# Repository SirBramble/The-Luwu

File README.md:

# The Luwu

ESP32 Board for RGB LED integration into Home Assistant

## Motivation

My 3D Printer has a standard RGB LED Strip installed in its enclosure. This Board allows me to control it with Home Assistant. There are easier and cheaper ways of doing this, but this Board also doubled as a test board for implementing Ideal Diodes and MOSFET drivers.

## Features

The Board uses a ESP32C3 to interface with Home Assistant. The ESP controls 3 RGB channels that are each capable of (in theory) driving 10A. These channels can also be mapped to control addressable RGB Strips, although this can only be done for all channels at once and **ONLY** if the level shifter logic voltage is set to 5V. There is also one dedicated addressable RGB Strip Port, that can be used at any time.

To accomplish these features, it needs a 5V supply to drive the logic and optionally the addressable LED Strips and a 12V supply to drive the non addressable Strip. To accomplish this in a 3D Printer environment a Voltage converter for the 24V Power Supply is needed. For this [the Supluwu](https://github.com/SirBramble/The-Supluwu) could be used.

## Integration into Home Assistant

ESP Home Config:

```yaml
esphome:
  name: NAME
  friendly_name: FRIENDLY_NAME

esp32:
  board: esp32-c3-devkitm-1
  framework:
    type: arduino

# Enable logging
logger:
  level: DEBUG
# Enable Home Assistant API
api:
  encryption:
    key: ""     #let this auto generate or set it yourself

ota:
  password: ""  #let this auto generate or set it yourself

wifi:
  ssid: !secret wifi_ssid
  password: !secret wifi_password

  # Enable fallback hotspot (captive portal) in case wifi connection fails
  ap:
    ssid: "FALLBACK_HOTSPOT_NAME"
    password: "SUPER_SECURE_PASSWORD123"

light:
  - platform: rgb
    id: oldstyle_rgb
    name: "Oldstyle RGB"
    red: gpio_red
    green: gpio_green
    blue: gpio_blue
    effects:
      - lambda:
          name: Rainbow
          update_interval: 5s
          lambda: |-
            static int state = 0;
            auto call = id(oldstyle_rgb).turn_on();
            call.set_transition_length(4000);
            if (state == 0) {
              call.set_rgb(1.0, 0.0, 0.0);
            } else if (state == 1) {
              call.set_rgb(1.0, 0.5, 0.0);
            } else if (state == 2) {
              call.set_rgb(1.0, 1.0, 0.0);
            } else if (state == 3) {
              call.set_rgb(0.5, 1.0, 0.0);
            } else if (state == 4) {
              call.set_rgb(0.0, 1.0, 0.0);
            } else if (state == 5) {
              call.set_rgb(0.0, 1.0, 0.5);
            } else if (state == 6) {
              call.set_rgb(0.0, 1.0, 1.0);
            } else if (state == 7) {
              call.set_rgb(0.0, 0.5, 1.0);
            } else if (state == 8) {
              call.set_rgb(0.0, 0.0, 1.0);
            } else if (state == 9) {
              call.set_rgb(0.5, 0.0, 1.0);
            } else if (state == 10) {
              call.set_rgb(1.0, 0.0, 1.0);
            } else if (state == 11) {
              call.set_rgb(1.0, 0.0, 0.5);
            }
            call.perform();
            state++;
            if (state == 12)
              state = 0;
      - lambda:
            name: Fast Rainbow
            update_interval: 1s
            lambda: |-
              static int state = 0;
              auto call = id(oldstyle_rgb).turn_on();
              call.set_transition_length(1000);
              if (state == 0) {
                call.set_rgb(1.0, 0.0, 0.0);
              } else if (state == 1) {
                call.set_rgb(1.0, 0.5, 0.0);
              } else if (state == 2) {
                call.set_rgb(1.0, 1.0, 0.0);
              } else if (state == 3) {
                call.set_rgb(0.5, 1.0, 0.0);
              } else if (state == 4) {
                call.set_rgb(0.0, 1.0, 0.0);
              } else if (state == 5) {
                call.set_rgb(0.0, 1.0, 0.5);
              } else if (state == 6) {
                call.set_rgb(0.0, 1.0, 1.0);
              } else if (state == 7) {
                call.set_rgb(0.0, 0.5, 1.0);
              } else if (state == 8) {
                call.set_rgb(0.0, 0.0, 1.0);
              } else if (state == 9) {
                call.set_rgb(0.5, 0.0, 1.0);
              } else if (state == 10) {
                call.set_rgb(1.0, 0.0, 1.0);
              } else if (state == 11) {
                call.set_rgb(1.0, 0.0, 0.5);
              }
              call.perform();
              state++;
              if (state == 12)
                state = 0;

# Example output entry (default)
output:
  - platform: ledc
    id: gpio_red
    pin: GPIO6
  - platform: ledc
    id: gpio_green
    pin: GPIO7
  - platform: ledc
    id: gpio_blue
    pin: GPIO10

#uncomment to enable
# Example output entry (modified)
#output:
#  - platform: ledc
#    id: gpio_red
#    pin: GPIO7
#  - platform: ledc
#    id: gpio_green
#    pin: GPIO10
#  - platform: ledc
#    id: gpio_blue
#    pin: GPIO6

captive_portal:
    
```

### Flashing firmware

I had some issues when flashing the Firmware.

This helped: [https://github.com/espressif/esp-idf/issues/9005](https://github.com/espressif/esp-idf/issues/9005)

## Schematic

The Schematic can be found here: [The Luwu PCB/print/The Luwu PCB.pdf](https://github.com/SirBramble/The-Luwu/blob/f4439437ab35bf7dc6665ce1337c5cff792b409b/The%20Luwu%20PCB/print/The%20Luwu%20PCB.pdf)

## Pictures

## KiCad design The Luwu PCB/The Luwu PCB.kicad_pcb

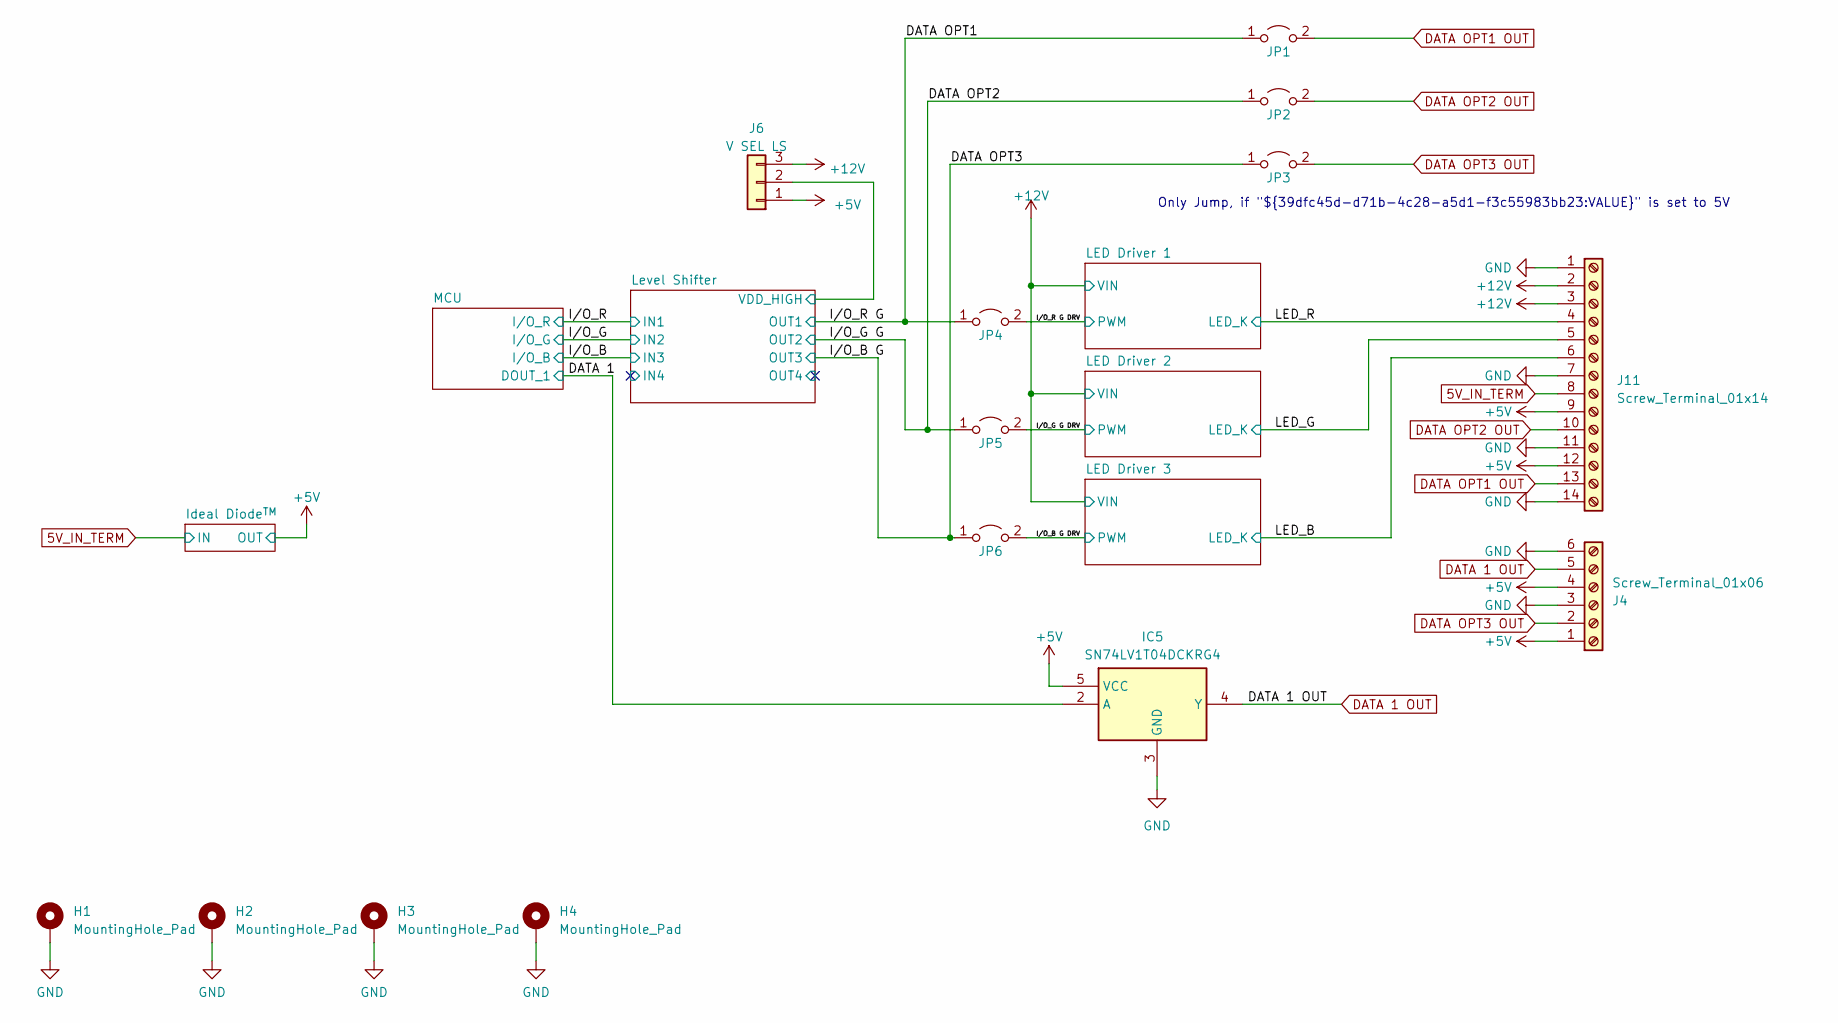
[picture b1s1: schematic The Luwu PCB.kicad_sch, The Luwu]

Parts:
H1, H2, H3, H4: MountingHole_Pad; MountingHole_3.2mm_M3_DIN965_Pad
IC5: SN74LV1T04DCKRG4; SOT65P210X110-5N; Mouser Part Number 595-SN74LV1T04DCKRG4
J4: Screw_Terminal_01x06; TerminalBlock_bornier-6_P5.08mm
J6: V SEL LS; PinHeader_1x03_P2.54mm_Vertical
J11: Screw_Terminal_01x14; TerminalBlock_bornier-14_P5.08mm
JP1, JP2, JP3, JP4, JP5, JP6: Jumper_2_Open; PinHeader_1x02_P2.54mm_Vertical

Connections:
5V_IN_TERM: J11.8; also elsewhere on the board
+5V: IC5.5 (VCC), J4.1, J4.4, J6.1, J11.9, J11.12; also elsewhere on the board
+12V: J6.3, J11.2, J11.3; also elsewhere on the board
/DATA 1: IC5.2 (A); also elsewhere on the board
/DATA OPT1: JP1.1 (A), JP4.1 (A); also elsewhere on the board
/DATA OPT2: JP2.1 (A), JP5.1 (A); also elsewhere on the board
/DATA OPT3: JP3.1 (A), JP6.1 (A); also elsewhere on the board
/I/O_B G DRV: JP6.2 (B); also elsewhere on the board
/I/O_G G DRV: JP5.2 (B); also elsewhere on the board
/I/O_R G DRV: JP4.2 (B); also elsewhere on the board
/LED_B: J11.6; also elsewhere on the board
/LED_G: J11.5; also elsewhere on the board
/LED_R: J11.4; also elsewhere on the board
/Level Shifter/VDD_HIGH: J6.2; also elsewhere on the board
DATA 1 OUT: IC5.4 (Y), J4.5
DATA OPT1 OUT: J11.13, JP1.2 (B)
DATA OPT2 OUT: J11.10, JP2.2 (B)
DATA OPT3 OUT: J4.2, JP3.2 (B)
GND: H1.1, H2.1, H3.1, H4.1, IC5.3 (GND), J4.3, J4.6, J11.1, J11.7, J11.11, J11.14; also elsewhere on the board

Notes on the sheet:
Only Jump, if "${39dfc45d-d71b-4c28-a5d1-f3c55983bb23:VALUE}" is set to 5V

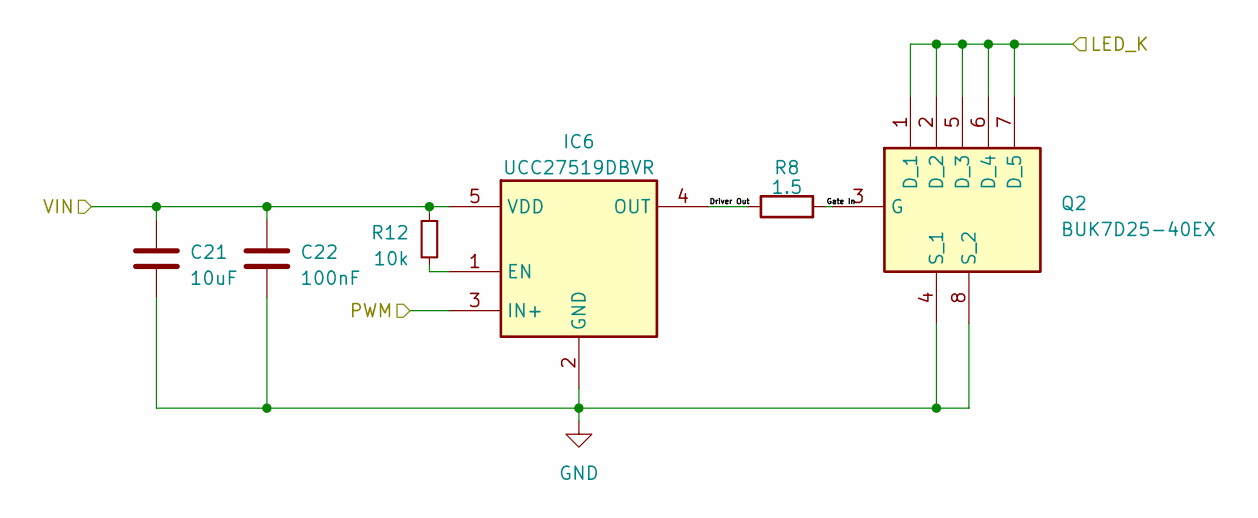
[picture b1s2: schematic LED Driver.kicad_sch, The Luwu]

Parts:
C21: 10uF; C_0603_1608Metric
C22: 100nF; C_0603_1608Metric
IC6: UCC27519DBVR; SOT95P280X145-5N; Mouser Part Number 595-UCC27519DBVR
Q2: BUK7D25-40EX; BUK7D2540EX; Mouser Part Number 771-BUK7D25-40EX
R8: 1.5; R_1206_3216Metric
R12: 10k; R_0603_1608Metric

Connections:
+12V: C21.1, C22.1, IC6.5 (VDD), R12.1; also elsewhere on the board
/I/O_R G DRV: IC6.3 (IN+); also elsewhere on the board
/LED Driver 1/Driver Out: IC6.4 (OUT), R8.1
/LED Driver 1/Gate In: Q2.3 (G), R8.2
/LED_R: Q2.1 (D_1), Q2.2 (D_2), Q2.5 (D_3), Q2.6 (D_4), Q2.7 (D_5); also elsewhere on the board
GND: C21.2, C22.2, IC6.2 (GND), Q2.4 (S_1), Q2.8 (S_2); also elsewhere on the board
unnamed: IC6.1 (EN), R12.2

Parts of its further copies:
C23, C25: 10uF; C_0603_1608Metric
C24, C26: 100nF; C_0603_1608Metric
IC7, IC8: UCC27519DBVR; SOT95P280X145-5N; Mouser Part Number 595-UCC27519DBVR
Q3, Q4: BUK7D25-40EX; BUK7D2540EX; Mouser Part Number 771-BUK7D25-40EX
R13, R15: 1.5; R_1206_3216Metric
R14, R16: 10k; R_0603_1608Metric

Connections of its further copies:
+12V: C23.1, C24.1, C25.1, C26.1, IC7.5 (VDD), IC8.5 (VDD), R14.1, R16.1; also elsewhere on the board
/I/O_B G DRV: IC8.3 (IN+); also elsewhere on the board
/I/O_G G DRV: IC7.3 (IN+); also elsewhere on the board
/LED Driver 2/Driver Out: IC7.4 (OUT), R13.1
/LED Driver 2/Gate In: Q3.3 (G), R13.2
/LED Driver 3/Driver Out: IC8.4 (OUT), R15.1
/LED Driver 3/Gate In: Q4.3 (G), R15.2
/LED_B: Q4.1 (D_1), Q4.2 (D_2), Q4.5 (D_3), Q4.6 (D_4), Q4.7 (D_5); also elsewhere on the board
/LED_G: Q3.1 (D_1), Q3.2 (D_2), Q3.5 (D_3), Q3.6 (D_4), Q3.7 (D_5); also elsewhere on the board
GND: C23.2, C24.2, C25.2, C26.2, IC7.2 (GND), IC8.2 (GND), Q3.4 (S_1), Q3.8 (S_2), Q4.4 (S_1), Q4.8 (S_2); also elsewhere on the board
unnamed: IC7.1 (EN), R14.2
unnamed: IC8.1 (EN), R16.2

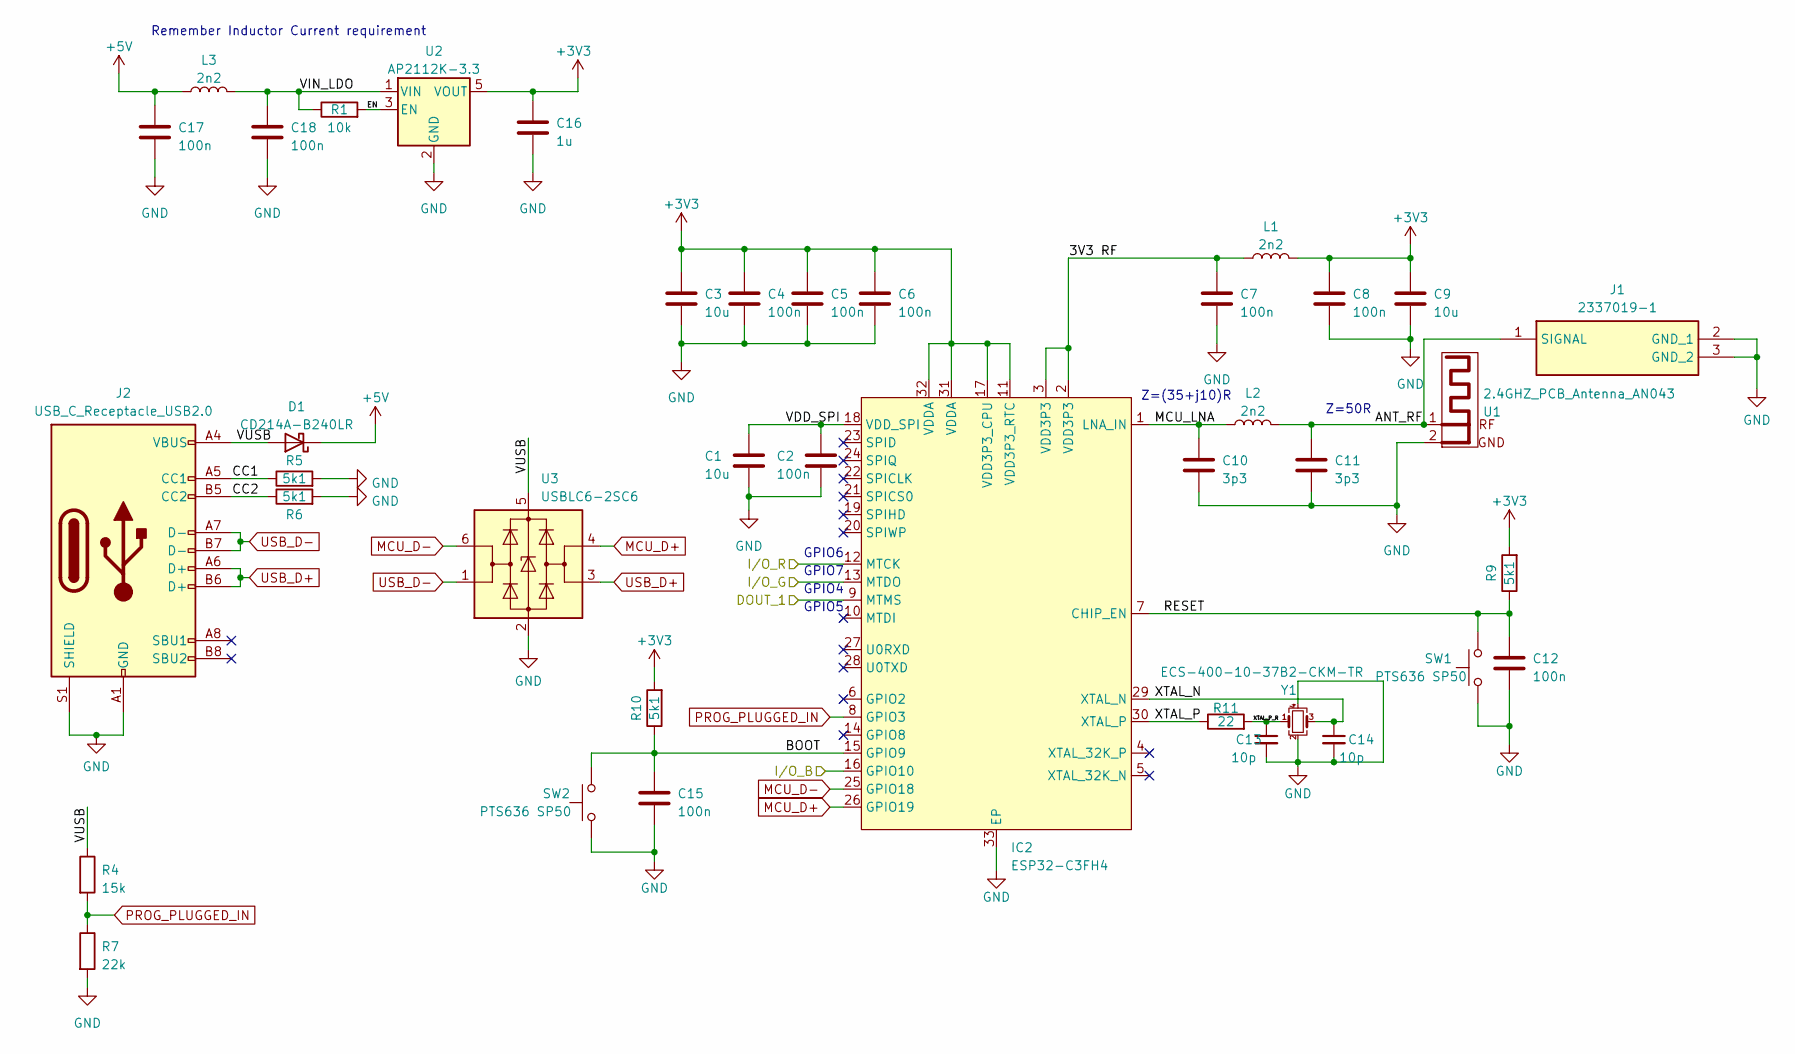
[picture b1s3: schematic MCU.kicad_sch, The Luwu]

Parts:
C1, C3, C9: 10u; C_0603_1608Metric
C2, C4, C5, C6, C7, C8, C12, C15, C17, C18: 100n; C_0603_1608Metric
C10, C11: 3p3; C_0603_1608Metric
C13, C14: 10p; C_0603_1608Metric
C16: 1u; C_0603_1608Metric
D1: CD214A-B240LR
IC2: ESP32-C3FH4; QFN50P500X500X90-33N-D; Mouser Part Number 356-ESP32-C3FH4
J1: 2337019-1; 23370191; Mouser Part Number 571-2337019-1
J2: USB_C_Receptacle_USB2.0; USB_C_Receptacle_GCT_USB4105-xx-A_16P_TopMnt_Horizontal
L1, L2, L3: 2n2; L_0603_1608Metric
R1: 10k; R_0603_1608Metric
R4: 15k; R_0603_1608Metric
R5, R6, R9, R10: 5k1; R_0603_1608Metric
R7: 22k; R_0603_1608Metric
R11: 22; R_0603_1608Metric
SW1, SW2: PTS636 SP50; PTS636SP50SMTRLFS
U1: 2.4GHZ_PCB_Antenna_AN043; 2.4GHZ PCB Antenna AN043
U2: AP2112K-3.3; SOT-23-5
U3: USBLC6-2SC6; SOT-23-6
Y1: ECS-400-10-37B2-CKM-TR; Crystal_SMD_2016-4Pin_2.0x1.6mm

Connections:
+3V3: C3.1, C4.1, C5.1, C6.1, C8.1, C9.1, C16.1, IC2.11 (VDD3P3_RTC), IC2.17 (VDD3P3_CPU), IC2.31 (VDDA), IC2.32 (VDDA), L1.2, R9.2, R10.2, U2.5 (VOUT); also elsewhere on the board
+5V: C17.1, D1.1 (K), L3.1; also elsewhere on the board
/DATA 1: IC2.9 (MTMS); also elsewhere on the board
/I/O_B: IC2.16 (GPIO10); also elsewhere on the board
/I/O_G: IC2.13 (MTDO); also elsewhere on the board
/I/O_R: IC2.12 (MTCK); also elsewhere on the board
/MCU/3V3 RF: C7.1, IC2.2 (VDD3P3), IC2.3 (VDD3P3), L1.1
/MCU/ANT_RF: C11.1, J1.1 (SIGNAL), L2.2, U1.1
/MCU/BOOT: C15.1, IC2.15 (GPIO9), R10.1, SW2.2
/MCU/CC1: J2.A5 (CC1), R5.1
/MCU/CC2: J2.B5 (CC2), R6.1
/MCU/EN: R1.2, U2.3 (EN)
/MCU/MCU_LNA: C10.1, IC2.1 (LNA_IN), L2.1
/MCU/RESET: C12.1, IC2.7 (CHIP_EN), R9.1, SW1.2
/MCU/VDD_SPI: C1.1, C2.1, IC2.18 (VDD_SPI)
/MCU/VIN_LDO: C18.1, L3.2, R1.1, U2.1 (VIN)
/MCU/VUSB: D1.2 (A), J2.A4 (VBUS), J2.A9 (VBUS), J2.B4 (VBUS), J2.B9 (VBUS), R4.1, U3.5 (VBUS)
/MCU/XTAL_N: C14.1, IC2.29 (XTAL_N), Y1.3
/MCU/XTAL_P: IC2.30 (XTAL_P), R11.1
/MCU/XTAL_P_R: C13.1, R11.2, Y1.1
GND: C1.2, C2.2, C3.2, C4.2, C5.2, C6.2, C7.2, C8.2, C9.2, C10.2, C11.2, C12.2, C13.2, C14.2, C15.2, C16.2, C17.2, C18.2, IC2.33 (EP), J1.2 (GND_1), J1.3 (GND_2), J2.A1 (GND), J2.A12 (GND), J2.B1 (GND), J2.B12 (GND), J2.S1 (SHIELD), R5.2, R6.2, R7.2, SW1.1, SW2.1, U1.2, U2.2 (GND), U3.2 (GND), Y1.2, Y1.4; also elsewhere on the board
MCU_D+: IC2.26 (GPIO19), U3.4 (I/O2)
MCU_D-: IC2.25 (GPIO18), U3.6 (I/O1)
PROG_PLUGGED_IN: IC2.8 (GPIO3), R4.2, R7.1
USB_D+: J2.A6 (D+), J2.B6 (D+), U3.3 (I/O2)
USB_D-: J2.A7 (D-), J2.B7 (D-), U3.1 (I/O1)

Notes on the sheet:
GPIO5
Remember Inductor Current requirement
GPIO4
Z=50R
GPIO7
Z=(35+j10)R
GPIO6

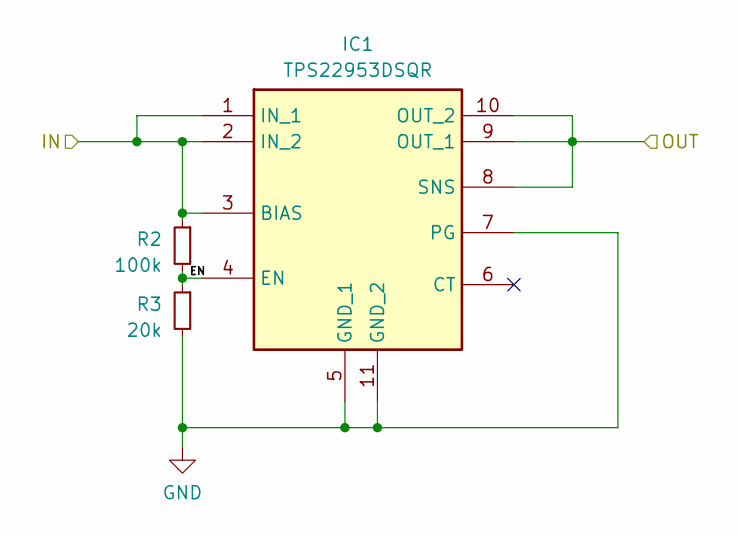
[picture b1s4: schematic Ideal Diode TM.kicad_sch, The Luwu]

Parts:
IC1: TPS22953DSQR; SON40P200X200X80-11N; Mouser Part Number 595-TPS22953DSQR
R2: 100k; R_0603_1608Metric
R3: 20k; R_0603_1608Metric

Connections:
5V_IN_TERM: IC1.1 (IN_1), IC1.2 (IN_2), IC1.3 (BIAS), R2.1; also elsewhere on the board
+5V: IC1.8 (SNS), IC1.9 (OUT_1), IC1.10 (OUT_2); also elsewhere on the board
/Ideal Diode^{TM}/EN: IC1.4 (EN), R2.2, R3.1
GND: IC1.5 (GND_1), IC1.7 (PG), IC1.11 (GND_2), R3.2; also elsewhere on the board

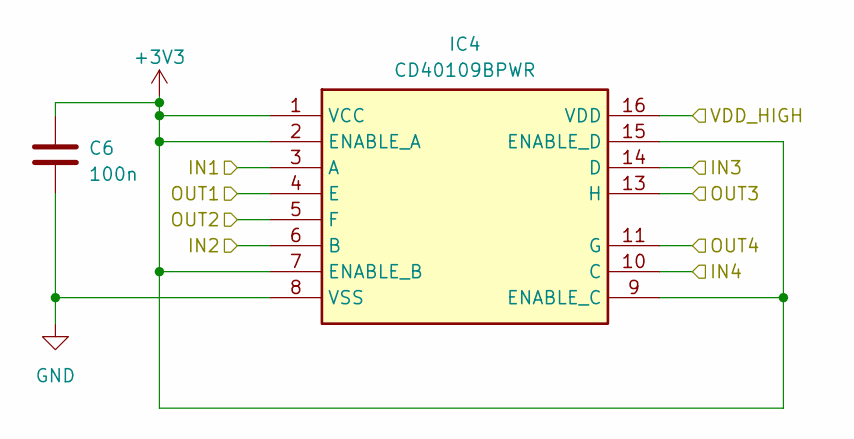
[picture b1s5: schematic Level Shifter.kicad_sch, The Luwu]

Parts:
C6: 100n; C_0603_1608Metric
IC4: CD40109BPWR; SOP65P640X120-16N; Mouser Part Number 595-CD40109BPWR

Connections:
+3V3: C6.1, IC4.1 (VCC), IC4.2 (ENABLE_A), IC4.7 (ENABLE_B), IC4.9 (ENABLE_C), IC4.15 (ENABLE_D); also elsewhere on the board
/DATA OPT1: IC4.4 (E); also elsewhere on the board
/DATA OPT2: IC4.5 (F); also elsewhere on the board
/DATA OPT3: IC4.13 (H); also elsewhere on the board
/I/O_B: IC4.14 (D); also elsewhere on the board
/I/O_G: IC4.6 (B); also elsewhere on the board
/I/O_R: IC4.3 (A); also elsewhere on the board
/Level Shifter/IN4: IC4.10 (C)
/Level Shifter/OUT4: IC4.11 (G)
/Level Shifter/VDD_HIGH: IC4.16 (VDD); also elsewhere on the board
GND: C6.2, IC4.8 (VSS); also elsewhere on the board

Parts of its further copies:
C19: 100n; C_0603_1608Metric

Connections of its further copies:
+3V3: C19.1; also elsewhere on the board
GND: C19.2; also elsewhere on the board

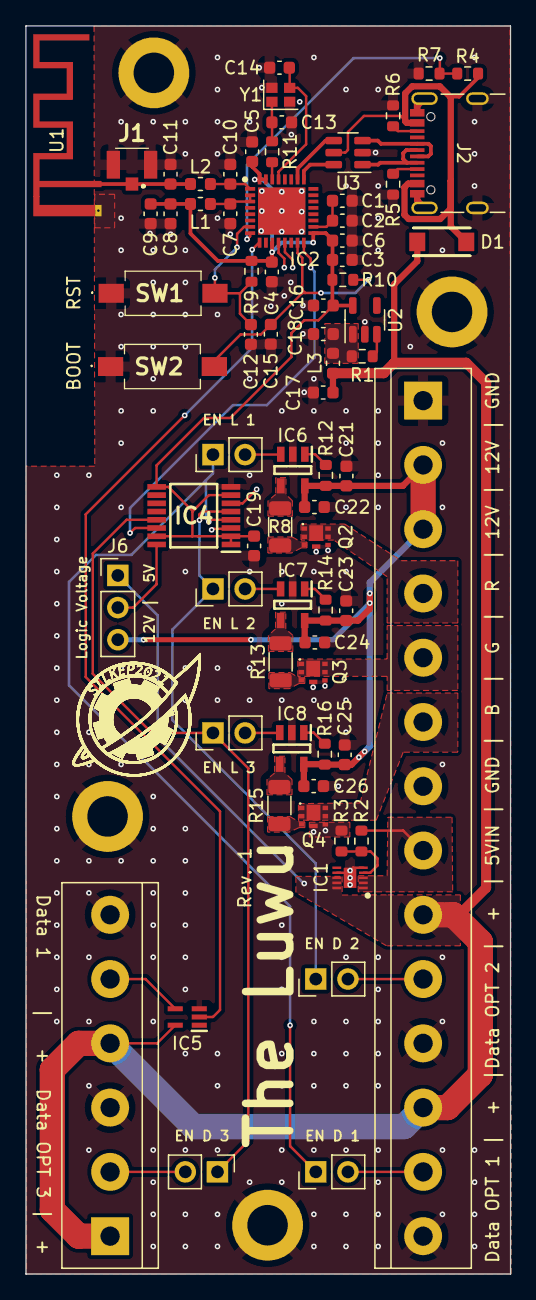
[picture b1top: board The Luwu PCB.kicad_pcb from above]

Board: 4 copper layers, 38.3 x 98.7 mm, 76 parts (0 on the bottom side), 52 nets.

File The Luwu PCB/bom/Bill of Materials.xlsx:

Designator | Footprint | Value | Description | Part Nr. | Quantity | Price/pcs. | Price
C10, C11 | 0603 | 3p3 | +/-0.5pF 50V Capacitor | 710-885012006048 | 2 | 9.2999999999999999E-2 | 0.186
C12, C15, C17, C18, C19, C2, C4, C5, C6, C7, C8 | 0603 | 100n | Generic 5% Capacitor | Generic | 11 | 0.01 | 0.11
C13, C14 | 0603 | 10p | 5% 25V Capacitor | 710-885012006032 | 2 | 9.2999999999999999E-2 | 0.186
C16 | 0603 | 1u | Generic 20% Capacitor | Generic | 1 | 0.05 | 0.05
C1, C3, C9, C21, C23, C25 | 0603 | 10uF | Generic 20% Capacitor | Generic | 6 | 0.05 | 0.30000000000000004
C22, C24, C26 | 0603 | 100nF | Generic 5% Capacitor | Generic | 3 | 0.01 | 0.03
D1 | CD214A-B240LR | CD214A-B240LR | 40V 2A Diode | 652-CD214A-B240LR | 1 | 0.39100000000000001 | 0.39100000000000001
IC1 | SON40P200X200X80-11N | TPS22953DSQR | Leistungsschalter IC | 595-TPS22953DSQR | 1 | 0.77200000000000002 | 0.77200000000000002
IC2 | QFN50P500X500X90-33N-D | ESP32-C3FH4 | ESP32C3 | 356-ESP32-C3FH4 | 1 | 1.21 | 1.21
IC4 | SOP65P640X120-16N | CD40109BPWR | 4-Bit Level shifter | 595-CD40109BPWR | 1 | 0.437 | 0.437
IC5 | SOT65P210X110-5N | SN74LV1T04DCKRG4 | 1-Bit Level shifter | 595-SN74LV1T04DCKRG4 | 1 | 0.214 | 0.214
IC6, IC7, IC8 | SOT95P280X145-5N | UCC27519DBVR | Gate driver | 595-UCC27519DBVR | 3 | 0.77200000000000002 | 2.3159999999999998
J1 | 23370191 | 2337019-1 | MicroCoax connector | 571-2337019-1 | 1 | 0.214 | 0.214
J10 | TerminalBlock_bornier-3_P5.08mm | Neopixel Terminal out 3 | Generic Terminal Block | Generic | 1 | 0.05 | 0.05
J2 | USB_C_Receptacle_GCT_USB4105-xx-A_16P_TopMnt_Horizontal | USB_C_Receptacle_USB2.0 | USB Type C 2.0 | 640-USB4105-GF-A | 1 | 0.74399999999999999 | 0.74399999999999999
J3 | TerminalBlock_bornier-2_P5.08mm | 5V_IN | Generic Terminal Block | Generic | 1 | 0.05 | 0.05
J4 | TerminalBlock_bornier-3_P5.08mm | Neopixel Terminal opt 1 | Generic Terminal Block | Generic | 1 | 0.05 | 0.05
J5 | TerminalBlock_bornier-2_P5.08mm | 12V_IN | Generic Terminal Block | Generic | 1 | 0.05 | 0.05
J6 | PinHeader_1x03_P2.54mm_Vertical | V SEL LS | Generic Pin Header | Generic | 1 | 0.05 | 0.05
J7 | TerminalBlock_bornier-4_P5.08mm | Screw_Terminal_01x04 | Generic Terminal Block | Generic | 1 | 0.05 | 0.05
J8 | TerminalBlock_bornier-3_P5.08mm | Neopixel Terminal | Generic Terminal Block | Generic | 1 | 0.05 | 0.05
J9 | TerminalBlock_bornier-3_P5.08mm | Neopixel Terminal opt 2 | Generic Terminal Block | Generic | 1 | 0.05 | 0.05
JP1, JP2, JP3, JP4, JP5, JP6 | PinHeader_1x02_P2.54mm_Vertical | Jumper_2_Open | Generic Pin Header | Generic | 6 | 0.05 | 0.30000000000000004
L1, L2, L3 | 0603 | 2n2 | 300mA 0,1ohm Inductor | 710-7847805220 | 3 | 9.2999999999999999E-2 | 0.27900000000000003
Q2, Q3, Q4 | BUK7D2540EX | BUK7D25-40EX | N-MOSFET | 771-BUK7D25-40EX | 3 | 0.251 | 0.753
R1, R12, R14, R16 | 0603 | 10k | Generic 1% Resistor | Generic | 4 | 0.02 | 0.08
R10, R5, R6, R9 | 0603 | 5k1 | Generic 1% Resistor | Generic | 4 | 0.02 | 0.08
R11 | 0603 | 22 | 1% Resistor | 603-RC0603FR-1022RL | 1 | 9.2999999999999999E-2 | 9.2999999999999999E-2
R13, R15, R8 | 1206 | 1.5 | Current shunt / Impulse limmiter | 652-CRM1206FX1R50ELF | 3 | 0.38100000000000001 | 1.143
R2 | 0603 | 100k | Generic 1% Resistor | Generic | 1 | 0.02 | 0.02
R3 | 0603 | 20k | 1% Resistor | 603-RT0603FRE0720KL | 1 | 9.2999999999999999E-2 | 9.2999999999999999E-2
R4 | 0603 | 15k | 1% Resistor | 603-RT0603FRE1315KL | 1 | 9.2999999999999999E-2 | 9.2999999999999999E-2
R7 | 0603 | 22k | 1% Resistor | 603-RT0603FRE1322KL | 1 | 9.2999999999999999E-2 | 9.2999999999999999E-2
SW1, SW2 | PTS636SP50SMTRLFS | PTS636 SP50 | Tact. Switch 12V 50mA | 611-PTS636SP50SMTRLF | 2 | 0.14000000000000001 | 0.28000000000000003
U2 | SOT-23-5 | AP2112K-3.3 | 3V3 Voltage Regulator | 621-AP2112K-3.3TRG1 | 1 | 0.307 | 0.307
U3 | SOT-23-6 | USBLC6-2SC6 | TVS Diode Usb | 511-USBLC6-2SC6 | 1 | 0.53900000000000003 | 0.53900000000000003
Y1 | Crystal_SMD_2016-4Pin_2.0x1.6mm | ECS-400-10-37B2-CKM-TR | Crystal 40MHz 10pF | 520-400-10-37B2CKMTR | 1 | 0.35299999999999998 | 0.35299999999999998
 |  |  |  |  |  |  | 12.065999999999999

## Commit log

2023-12-30 added TN
2023-12-30 added schmatic
2023-12-30 added shortcut for schematic
2023-12-30 removed shortcut
2023-12-30 updated schematic print
2023-12-30 updated size
2023-12-31 updated pictures
2024-01-21 added 3D
2024-01-24 added ESPHOME config
